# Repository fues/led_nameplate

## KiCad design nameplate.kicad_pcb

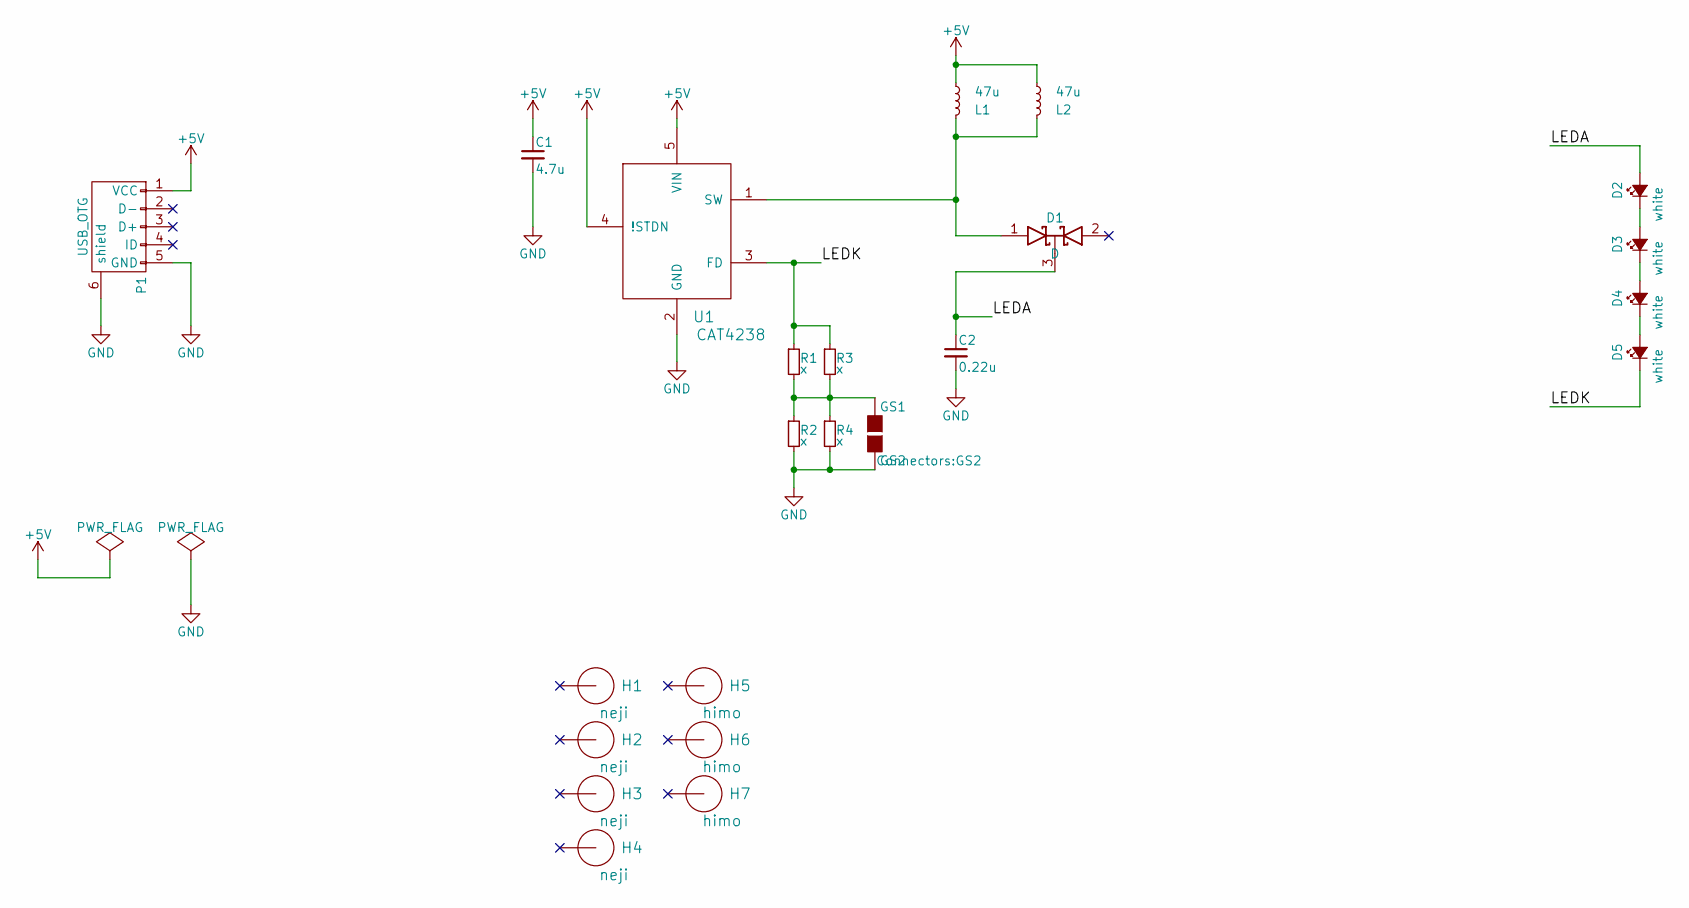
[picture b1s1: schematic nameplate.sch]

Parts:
C1: 4.7u; C_0805_HandSoldering
C2: 0.22u; C_0603_HandSoldering
D1: D; SC-59_Handsoldering
D2, D3, D4, D5: white; NSCW008AT
GS1: GS2
H1, H2, H3, H4: neji; M3-drillHole_5mm_nosilk
H5, H6, H7: himo; M3-drillHole_5mm_nosilk
L1: 47u; Choke_SMD_10.4x10.4_H4.8
L2: 47u; Choke_SMD_6.3x6.3_H3
P1: USB_OTG; ZX62R-B-5P
R1, R2, R3, R4: x; R_0603
U1: CAT4238; SOT-23-5

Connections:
+5V: C1.1, L1.1, L2.1, P1.1 (VCC), U1.4 (!STDN), U1.5 (VIN)
/LEDA: C2.1, D1.3 (K), D2.2 (A)
/LEDK: D5.1 (K), R1.1, R3.1, U1.3 (FD)
GND: C1.2, C2.2, GS1.2 (G2), P1.5 (GND), P1.6 (shield), R2.2, R4.2, U1.2 (GND)
unnamed: D1.1 (A), L1.2, L2.2, U1.1 (SW)
unnamed: D2.1 (K), D3.2 (A)
unnamed: D3.1 (K), D4.2 (A)
unnamed: D4.1 (K), D5.2 (A)
unnamed: GS1.1 (G1), R1.2, R2.1, R3.2, R4.1

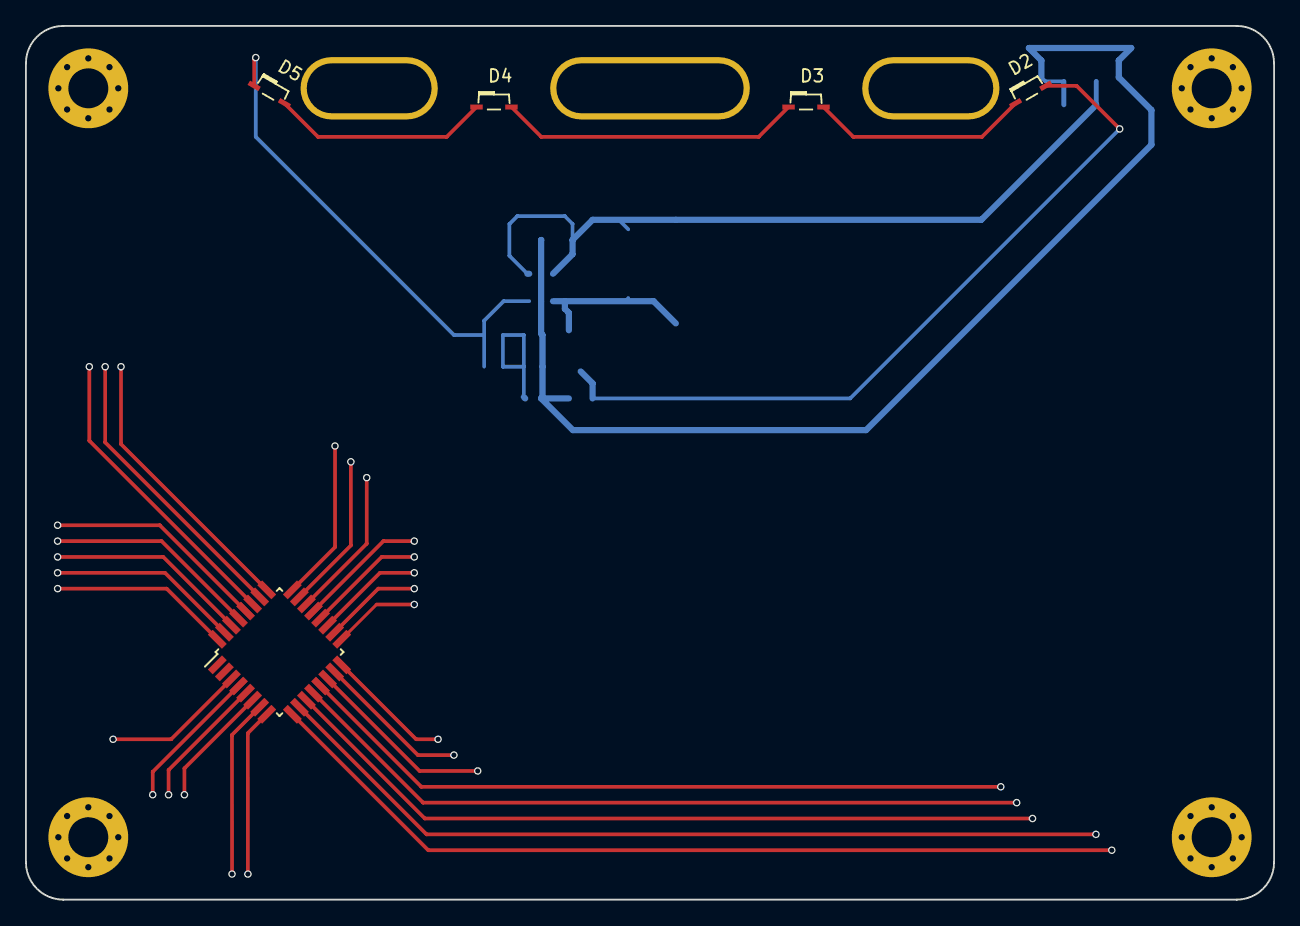
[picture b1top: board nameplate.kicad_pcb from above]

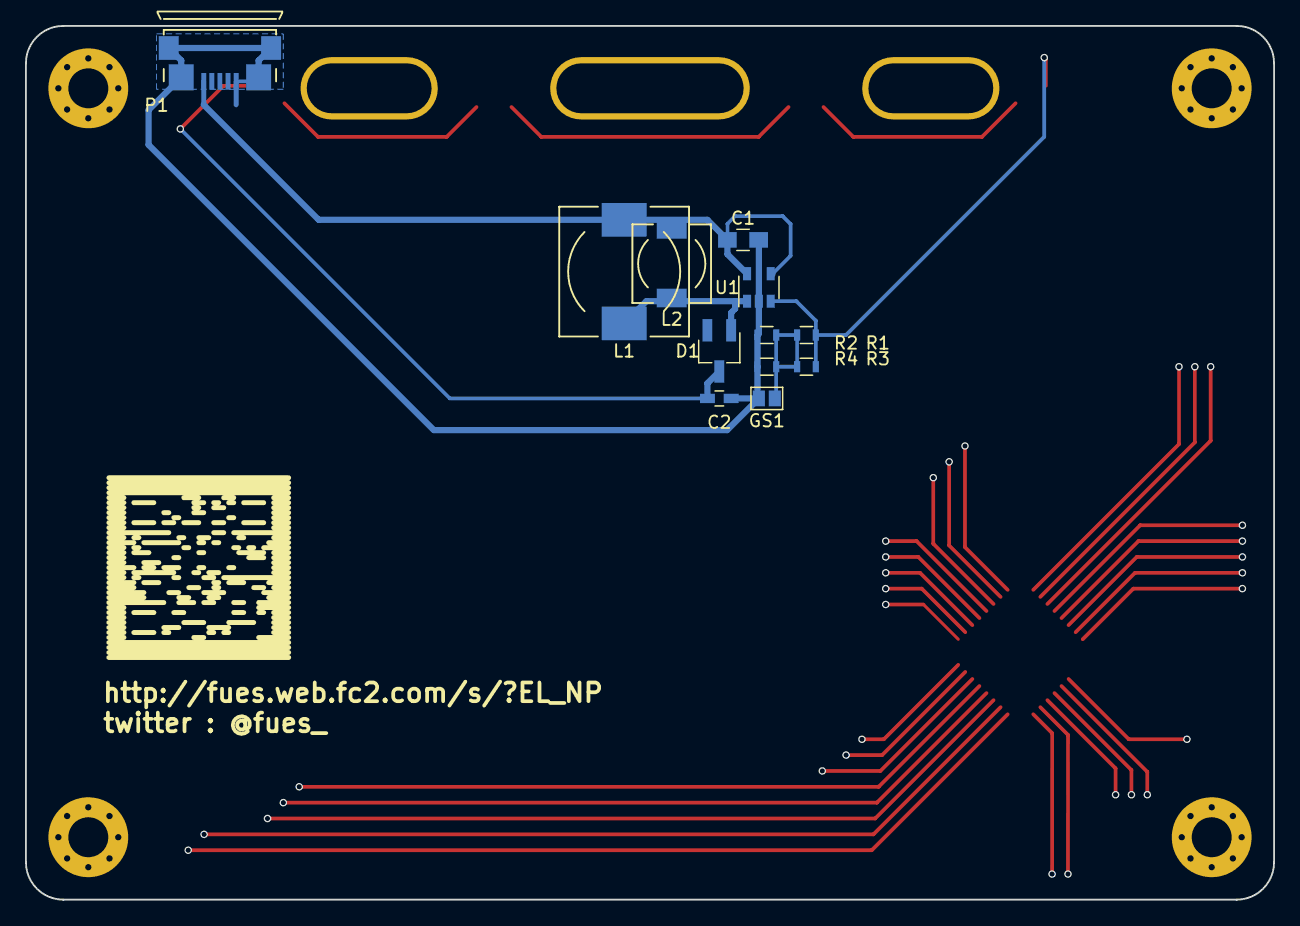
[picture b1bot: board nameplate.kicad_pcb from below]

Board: 2 copper layers, 100.0 x 70.0 mm, 23 parts (12 on the bottom side), 9 nets.

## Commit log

2018-03-30 リポジトリ作成
